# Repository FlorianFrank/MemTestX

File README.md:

<div style="text-align: center;">  </div>

</br>

This work is based on the publication **Reconfigurable Hardware Platform for Characterizing Physical Unclonable Functions in Non-Volatile Memories**, which is currently under review:

> **Abstract:**  
> Physical Unclonable Functions (PUFs) are widely recognized for deriving strong cryptographic keys from inherent manufacturing variations in hardware.  
> A popular class of PUFs is extracted from memory modules already integrated into computing systems, offering a cost-efficient method for generating strong cryptographic keys. Various techniques exist for extracting PUF responses from such memory modules, including repeated row activation and exploitation of charge leakage effects (known as row hammering), variations in supply voltage, intentional violations of memory timing specifications, as well as the use of random startup values and data retention characteristics. To perform such experiments—especially on novel non-volatile memory modules—a dedicated measurement ecosystem is required, which is presented in this work. The proposed setup uses a custom PCB to connect different types of memories to reconfigurable hardware. An optimized hardware design was developed and deployed on the reconfigurable hardware, enabling the execution of PUF experiments on various memory modules. The system allows for dynamic adjustment of timing specifications and voltage levels, even during experiment execution. Finally, a program is provided that schedules the experiments, retrieves the results, and enables persistent storage and evaluation methods.

This repository contains all components required for an extensive evaluation of memory-based PUFs, with a focus on emerging memory technologies such as FRAM, MRAM, and ReRAM. The setup is built based on an AMD ZCU102 FPGA and is designed to interface with any memory device featuring an SRAM-compatible parallel interface.

The various components included in this repository are illustrated in the following figure:

<div style="text-align: center;">  </div>

The components are divided into **hardware** and **software** components, following the structure of this repository.  

### Hardware

The **hardware** folder contains:  

- **FMC Adapter PCB Layout:**  
  A PCB adapter designed to interface various memory modules with the ZCU102 through its FMC connector. It supports memories with up to 24 address lines and 16 data lines and bridges the logic voltage level differences between the ZCU102 and the connected memory modules. Additionally, it provides options for connecting external power supplies and includes debugging interfaces. The design prioritizes signal integrity and minimizes glitches and noise.

- **Memory Adapter Reference Design:**
A reference adapter board currently configured for the Lapis Semiconductor MR48V256C memory module, designed to interface with the FMC adapter PCB. This folder contains a short tutorial on how to adjust the board for other memory footprints.

- **FPGA Design:**  
  Contains the FPGA design implementing a custom SRAM memory controller with all timing parameters adjustable at runtime. It supports several types of experiments, including rowhammering as well as read and write latency variations. Timing parameters can be tuned with a granularity of 2.5 nanoseconds. The design also includes an AXI interface for communication with the ZCU102’s processing system.

### Software

The **software** folder contains:  

- **PS Software:**  
  Implements the firmware running on the Processing System (PS) of the ZCU102. It manages communication with the PL to schedule and control experiments, as well as to receive measurement data through the same interface.  
  Additionally, it provides a network interface for receiving commands and parameters from an external experiment scheduler (described below). The firmware also transmits the collected measurement data back to this external program for persistent storage and further analysis.

- **Experiment Scheduler:**  
  A program that runs on an external computer connected to the ZCU102 via Ethernet. It allows the definition of various experiments and hardware classes (e.g., specific memory models), as well as instances of those classes. The scheduler manages the execution of experiments on these instances, delegating them either to the PS Software on the ZCU102 or to a microcontroller-based reference setup (described next).  
  It also collects the resulting measurement data, stores it persistently, and keeps track of the experiments executed for each hardware instance.

- **Microcontroller-Based Setup:**  
  An implementation running on an STM32F429 microcontroller with an integrated memory controller, capable of executing the same set of experiments as the ZCU102. However, this setup is constrained by the significantly lower clock frequency of its memory controller (120 MHz compared to 400 MHz on the FPGA). Communication with the experiment scheduler is established via a UART interface.

- **GUI support:**

## Quick Setup

The following provides the basic information to setup the memory evaluator. 

### Prerequisites

To build the PCB, **KiCad version 6** is required.  
To build the FPGA design and PS firmware, **Xilinx Vivado 2022.2** with **Vitis** must be installed as well as a **CMake** build system.
Note that generating the bitstream for the **ZCU102** requires the **Vivado ML Enterprise Edition**.  

The scheduler requires at least **Python 3.10**.  

A detailed list of all dependencies can be found in the respective component folders.

### PCB Production

To produce the PCB, navigate to `hardware/pcbs/fmc_memory_adapter`. The export folder contains the compressed Gerber files, which can be uploaded to your preferred PCB manufacturer.
The required components are listed in the **bill_of_material** folder.

### MPSoC Setup

To set up the FPGA and the corresponding firmware on the processing system, we provide a script that automates all required steps.  
Simply run the following commands:

```bash
cd scripts
./setup_and_run_environment.sh
```

This script performs the steps illustrated in the following diagram:

<div style="text-align: center;">  </div>

> ⚠️ This script has been verified only on **Ubuntu 22.10**, with **Vivado** installed in `/opt/Xilinx`.  
> To run it in a different environment, adjustments to the `VIVADO_PATH` variable or direct execution of the `.tcl` scripts may be necessary.

Furthermore, as shown in the figure above, the `./setup_and_run_environment.sh` script directly invokes several other scripts displayed at the bottom.  
These scripts can also be executed manually.  
Additional information about each script can be found in the respective folders containing them.

### Microcontroller-based Setup

To compile the microcontroller-based setup located in `software/memory_evaluator_stm32f429`, we provide a Docker-based build process.  
This approach eliminates the need to install the full toolchain on your local machine.  

First, build the Docker image by running:

```bash
cd software/memory_evaluator_stm32f429
docker build -t stm32f429-build .
```

Then, compile the firmware by executing:

```bash
./compile_fw_docker.sh
```

This command will start the Docker container, compile the firmware, and copy the resulting `MemoryController.elf` into the `software/memory_evaluator_stm32f429/bin` folder.

To flash the device, OpenOCD integrated within the CLion IDE was used. For more details, refer to the [`README.md`](/software/memory_evaluator_stm32f429/README.md) file found within the respective folder.

### Run the Scheduler (standalone)

All necessary dependencies for the scheduler can be installed by running:

```bash
cd software/experiment_scheduler/scripts
./setup.sh
```

To start the scheduler, simply execute:

```bash
cd software/experiment_scheduler/scripts
./run.sh <test_specification>.yaml
```

More information about the test specification format can be found in the scheduler’s [`README.md`](/software/experiment_scheduler/README.md) file.

### Run the Scheduler (with GUI Support)

Our microcontroller can be connected to a graphical user interface to define tests, schedule and monitor their execution.

#### Checkout the Backend and GUI 

If you are working from the Zenodo archive, you need to manually clone the backend and GUI:

```bash
cd software
git clone git@github.com:FlorianFrank/experiment_execution_hub.git
cd experiment_execution_hub
git sumbmodule update --init --recursive
```
If you instead cloned the GitHub repository with submodules, the backend and GUI are already present in the software folder and no additional setup is required.

#### Start the Backend and GUI

From inside the ```experiment_execution_hub``` directory, start the Django backend and the React frontend using Docker:

```bash
docker compose up
```
This will launch the: 
  - nats broker to connect multiple schedulers with the GUI
  - the Django backend (API and services), and
  - the React frontend (web-based GUI).

Afterwards you can see the gui when opening

[http://localhost:8000](http://localhost:8000)

Detailed information can be found in the repositories documentation [https://github.com/FlorianFrank/experiment_execution_hub](https://github.com/FlorianFrank/experiment_execution_hub)

as well as on a decicated documentation website [https://test-automation.florian-frank.com](https://test-automation.florian-frank.com)

To run the microservice go to ```software/experiment_scheduler``` from the root direcory and simply run:

```bash
./run_microservice.bash
```

Make sure the microservice is configured the right way (see the dedicated documentation in ```software/experiment_scheduler```)

## Contact

If you encounter any issues or errors, please open an issue on this page or contact me at:  **florian.frank(at)uni-passau.de**

## Release Notes
---

See the [changelog](CHANGELOG.md) for changes between versions.

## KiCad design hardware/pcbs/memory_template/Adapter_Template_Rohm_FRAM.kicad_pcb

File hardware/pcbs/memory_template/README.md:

### Memory Template PCB Design

This directory contains a reference adapter board design that can be adapted to different memory types. The current implementation targets the [Lapis Semiconductor MR48V256C](https://www.mouser.de/datasheet/2/348/ROHM-06-04-2018-FEDR48V256C-01-1500402.pdf) FRAM memory module.

A 3D rendering of the board is shown below:

#### Customization for Other Memory Modules
To adapt the design to a different memory device (including alternative packages):

1. Open the KiCad Project (`Adapter_Template_Rohm_FRAM.pro`)

The design was created using **KiCad 8.0.7.**

2. Open the schematic 
    - Identify the two 2×32-pin connectors on the left and right:
        - These connect to the FMC adapter board.
        - **Do not modify these connectors.**
    - Locate the symbol reprenting the memory module in the center: 
        - Either modify the symbol to fit your footprint or
        - adjust the footprint to match the existing symbol

The schematic is shown below for reference:

3. Open the Footprint Editor in KiCad.

To adapt the footprint: 

- Create a new footprint or import an existing one (e.g. from [Component Search Engine](https://componentsearchengine.com))
- Now adjust the pad number so that they match with the ones from the symbol as shown below.

4. Assign the footprint to Symbol U2

5. Export the Netlist `File -> Export -> Netlist``

6. Open the PCB design (`Adapter_Template_Rohm_FRAM.kicad_pcb`)

7. Import the netlist and route the design. 
    > Rooting may be automized for example by using [freerouting](https://www.freerouting.app)

Figure of the reference PCB design: 

8. Now you can export your Design as Gerber file and produce it as cost efficient two layer PCB.

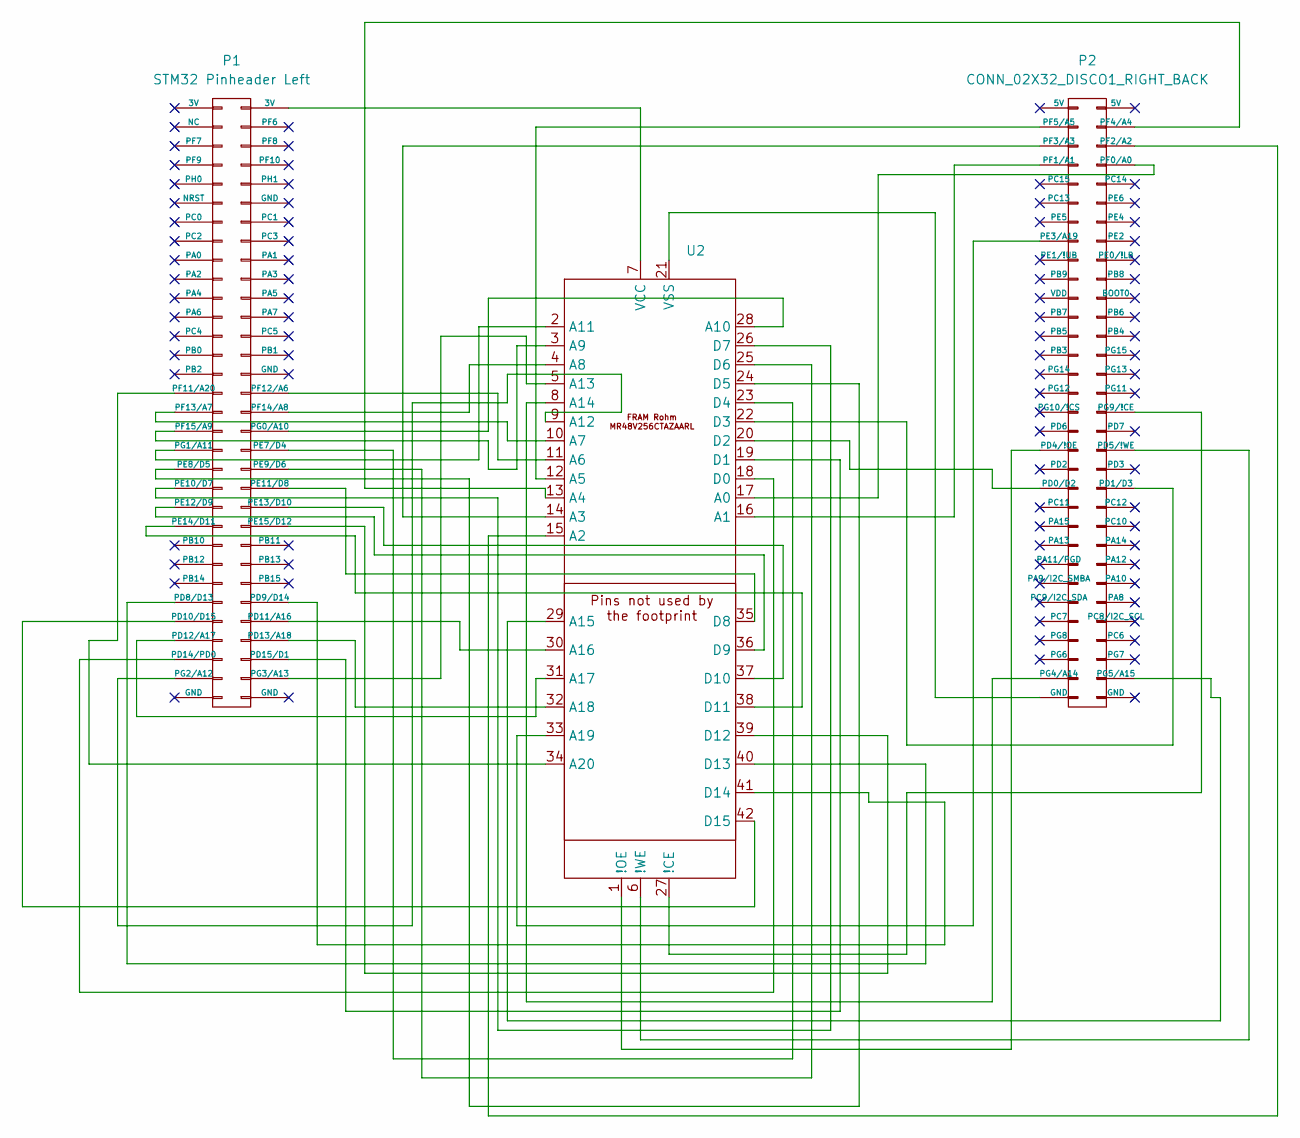
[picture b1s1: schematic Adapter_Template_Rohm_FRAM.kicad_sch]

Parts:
P1: STM32 Pinheader Left; PinHeader_2x32_P2.54mm_Vertical
P2: CONN_02X32_DISCO1_RIGHT_BACK; PinHeader_2x32_P2.54mm_Vertical
U2: TSOP-1 MR48V256CTAZAARL

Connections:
unnamed: P1.53 (PD8/D13), U2.40 (D13)
unnamed: P1.54 (PD9/D14), U2.41 (D14)
unnamed: P1.55 (PD10/D15), U2.42 (D15)
unnamed: P1.56 (PD11/A16), U2.30 (A16)
unnamed: P1.57 (PD12/A17), U2.31 (A17)
unnamed: P1.58 (PD13/A18), U2.32 (A18)
unnamed: P1.59 (PD14/PD0), U2.18 (D0)
unnamed: P1.60 (PD15/D1), U2.19 (D1)
unnamed: P1.38 (PE7/D4), U2.23 (D4)
unnamed: P1.39 (PE8/D5), U2.24 (D5)
unnamed: P1.40 (PE9/D6), U2.25 (D6)
unnamed: P1.41 (PE10/D7), U2.26 (D7)
unnamed: P1.42 (PE11/D8), U2.35 (D8)
unnamed: P1.43 (PE12/D9), U2.36 (D9)
unnamed: P1.44 (PE13/D10), U2.37 (D10)
unnamed: P1.45 (PE14/D11), U2.38 (D11)
unnamed: P1.46 (PE15/D12), U2.39 (D12)
unnamed: P1.31 (PF11/A20), U2.34 (A20)
unnamed: P1.32 (PF12/A6), U2.11 (A6)
unnamed: P1.33 (PF13/A7), U2.10 (A7)
unnamed: P1.34 (PF14/A8), U2.4 (A8)
unnamed: P1.35 (PF15/A9), U2.3 (A9)
unnamed: P1.36 (PG0/A10), U2.28 (A10)
unnamed: P1.37 (PG1/A11), U2.2 (A11)
unnamed: P1.61 (PG2/A12), U2.9 (A12)
unnamed: P1.62 (PG3/A13), U2.5 (A13)
unnamed: P2.41 (PD0/D2), U2.20 (D2)
unnamed: P2.42 (PD1/D3), U2.22 (D3)
unnamed: P2.37 (PD4/!OE), U2.1 (!OE)
unnamed: P2.38 (PD5/!WE), U2.6 (!WE)
unnamed: P2.15 (PE3/A19), U2.33 (A19)
unnamed: P2.8 (PF0/A0), U2.17 (A0)
unnamed: P2.7 (PF1/A1), U2.16 (A1)
unnamed: P2.6 (PF2/A2), U2.15 (A2)
unnamed: P2.5 (PF3/A3), U2.14 (A3)
unnamed: P2.4 (PF4/A4), U2.13 (A4)
unnamed: P2.3 (PF5/A5), U2.12 (A5)
unnamed: P2.61 (PG4/A14), U2.8 (A14)
unnamed: P2.62 (PG5/A15), U2.29 (A15)
unnamed: P2.34 (PG9/!CE), U2.27 (!CE)
unnamed: P1.2 (3V), U2.7 (VCC)
unnamed: P2.63 (GND), U2.21 (VSS)

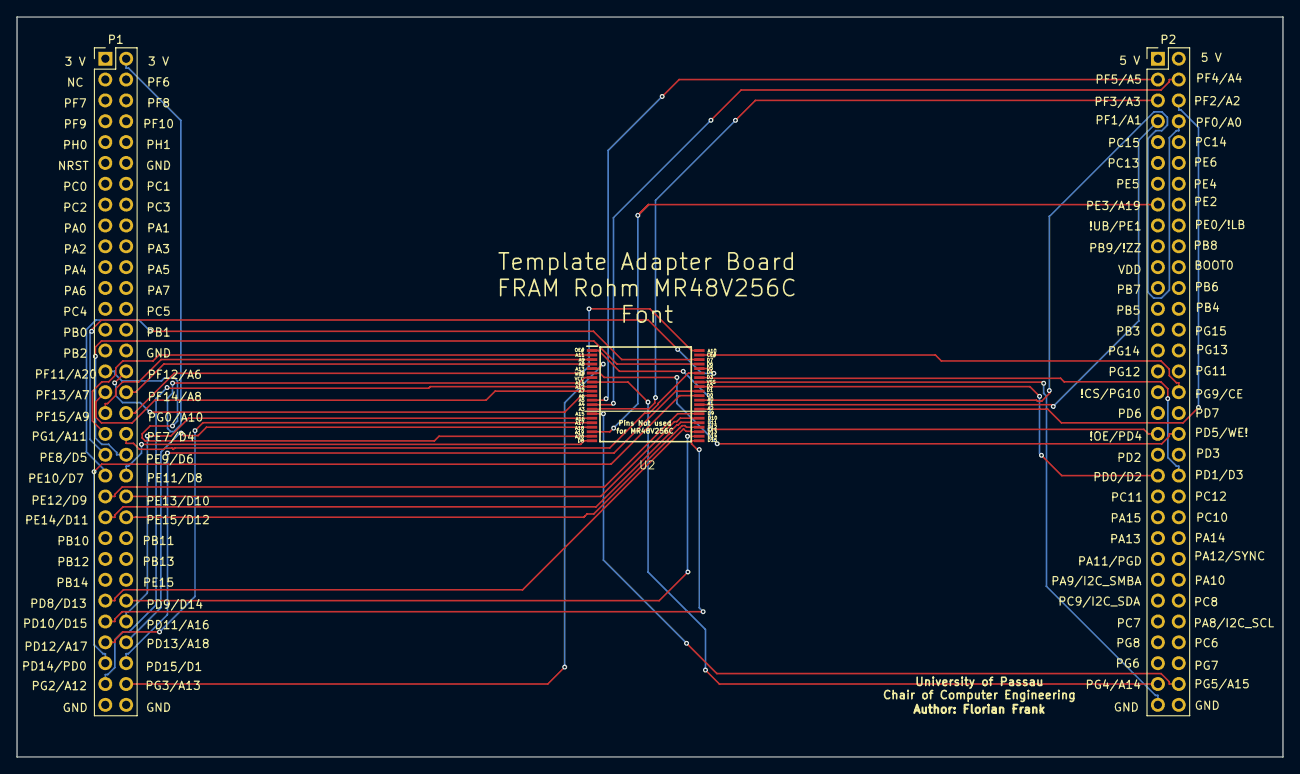
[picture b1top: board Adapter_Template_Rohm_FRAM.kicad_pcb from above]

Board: 2 copper layers, 154.3 x 90.2 mm, 3 parts (0 on the bottom side), 42 nets.

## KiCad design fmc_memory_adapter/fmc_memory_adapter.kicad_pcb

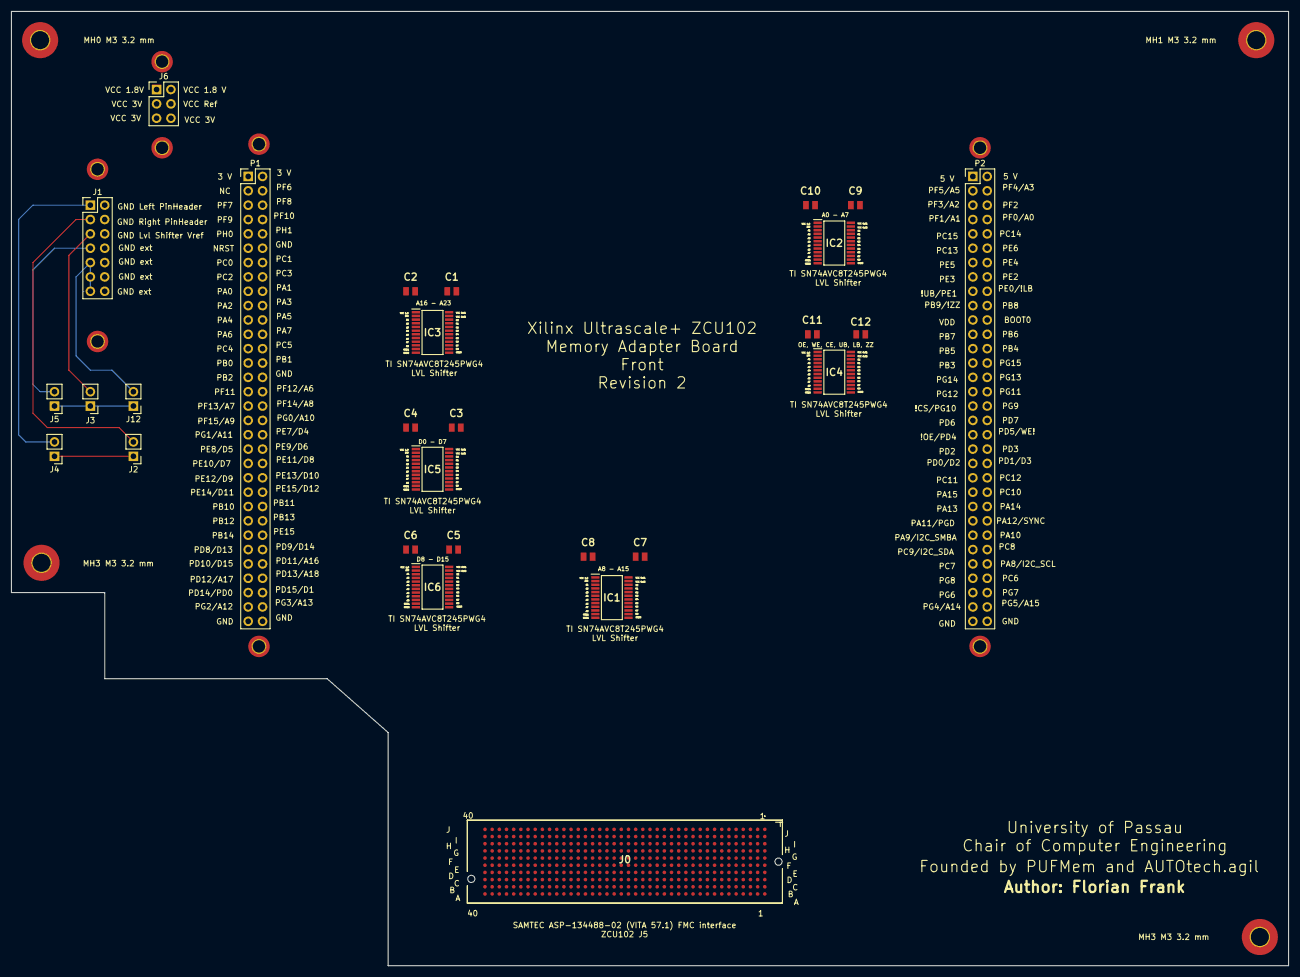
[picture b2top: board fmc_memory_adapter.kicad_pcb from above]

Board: 2 copper layers, 226.1 x 168.9 mm, 40 parts (0 on the bottom side), 109 nets.

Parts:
 : MountingHole_2.2mm_M2_DIN965_Pad_TopBottom
 #2,  #3,  #4,  #5,  #6,  #7,  #8: MountingHole_2.2mm_M2_DIN965_Pad_TopBottom
C1, C2, C3, C4, C5, C6, C7, C8, C9, C10, C11, C12: C0805C104K5RAC7411; CAPC2012X88N
IC1, IC2, IC3, IC4, IC5, IC6: SN74AVC8T245PWG4; SOP65P640X120-24N
J0: ASP-134488-02; ASP13448802
J1: Conn_02x07_Odd_Even; PinHeader_2x07_P2.54mm_Vertical
J2: GND_Jumper2; PinHeader_1x02_P2.54mm_Vertical
J3: GND_Jumper3; PinHeader_1x02_P2.54mm_Vertical
J4: GND_Jumper1; PinHeader_1x02_P2.54mm_Vertical
J5: GND_Jumper4; PinHeader_1x02_P2.54mm_Vertical
J6: Voltage_Selector; PinHeader_2x03_P2.54mm_Vertical
J12: GND_Jumper5; PinHeader_1x02_P2.54mm_Vertical
MH0 M3 3.2 mm, MH1 M3 3.2 mm, MH3 M3 3.2 mm, MH3 M3 3.2 mm#2: MountingHole_3.2mm_M3_Pad_TopBottom
P1: CONN_02X32_DISCO1_LEFT_BACK; PinHeader_2x32_P2.54mm_Vertical
P2: CONN_02X32_DISCO1_RIGHT_BACK; PinHeader_2x32_P2.54mm_Vertical

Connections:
unnamed: IC1.3 (A1), J0.G6
unnamed: IC1.4 (A2), J0.G7
unnamed: IC1.5 (A3), J0.G9
unnamed: IC1.6 (A4), J0.G10
unnamed: IC1.7 (A5), J0.G12
unnamed: IC1.8 (A6), J0.G13
unnamed: IC1.9 (A7), J0.G15
unnamed: IC1.10 (A8), J0.G16
unnamed: IC1.21 (B1), P1.34 (PF14)
unnamed: IC1.20 (B2), P1.35 (PF15)
unnamed: IC1.19 (B3), P1.36 (PG0)
unnamed: IC1.18 (B4), P1.37 (PG1)
unnamed: IC1.17 (B5), P1.61 (PG2)
unnamed: IC1.16 (B6), P1.62 (PG3)
unnamed: IC1.15 (B7), P2.61 (PG4)
unnamed: IC1.14 (B8), P2.62 (PG5)
unnamed: IC1.2 (DIR), IC2.2 (DIR), IC3.2 (DIR), IC4.2 (DIR), J0.H10
unnamed: C1.2, C2.2, C3.1, C4.1, C5.1, C6.1, C7.1, C8.1, C9.1, C10.1, C11.1, C12.1, IC1.11 (GND_1), IC1.12 (GND_2), IC1.13 (GND_3), IC2.11 (GND_1), IC2.12 (GND_2), IC2.13 (GND_3), IC3.11 (GND_1), IC3.12 (GND_2), IC3.13 (GND_3), IC4.11 (GND_1), IC4.12 (GND_2), IC4.13 (GND_3), IC5.11 (GND_1), IC5.12 (GND_2), IC5.13 (GND_3), IC6.5 (A3), IC6.11 (GND_1), IC6.12 (GND_2), J0.D8, J1.6
unnamed: C2.1, C3.2, C4.2, C5.2, C8.2, C9.2, C12.2, IC1.1 (VCCA), IC2.1 (VCCA), IC3.1 (VCCA), IC4.1 (VCCA), IC5.1 (VCCA), IC6.1 (VCCA), IC6.23 (VCCB_1), IC6.24 (VCCB_2), J6.2
unnamed: C1.1, C6.2, C7.2, C10.2, C11.2, IC1.23 (VCCB_1), IC1.24 (VCCB_2), IC2.23 (VCCB_1), IC2.24 (VCCB_2), IC3.23 (VCCB_1), IC3.24 (VCCB_2), IC4.23 (VCCB_1), IC4.24 (VCCB_2), IC5.23 (VCCB_1), IC5.24 (VCCB_2), J6.4
unnamed: IC1.22 (~OE), IC2.22 (~OE), IC3.22 (~OE), IC4.22 (~OE), IC5.22 (~OE), IC6.22 (~OE), J0.H7
unnamed: IC2.3 (A1), J0.D17
unnamed: IC2.4 (A2), J0.D18
unnamed: IC2.5 (A3), J0.D20
unnamed: IC2.6 (A4), J0.D21
unnamed: IC2.7 (A5), J0.D23
unnamed: IC2.8 (A6), J0.D24
unnamed: IC2.9 (A7), J0.D26
unnamed: IC2.10 (A8), J0.D27
unnamed: IC2.21 (B1), P2.8 (PF0)
unnamed: IC2.20 (B2), P2.7 (PF1)
unnamed: IC2.19 (B3), P2.6 (PF2)
unnamed: IC2.18 (B4), P2.5 (PF3)
unnamed: IC2.17 (B5), J1.4, P2.4 (PF4), P2.63 (GND), P2.64 (GND)
unnamed: IC2.16 (B6), P2.3 (PF5)
unnamed: IC2.15 (B7), P1.32 (PF12)
unnamed: IC2.14 (B8), P1.33 (PF13)
unnamed: IC3.3 (A1), J0.G18
unnamed: IC3.4 (A2), J0.G19
unnamed: IC3.5 (A3), J0.G21
unnamed: IC3.6 (A4), J0.G22
unnamed: IC3.7 (A5), J0.G24
unnamed: IC3.8 (A6), J0.G25
unnamed: IC3.9 (A7), J0.G27
unnamed: IC3.10 (A8), J0.G28
unnamed: IC3.21 (B1), P1.56 (PD11)
unnamed: IC3.20 (B2), P1.57 (PD12)
unnamed: IC3.19 (B3), P1.58 (PD13)
unnamed: IC3.18 (B4), P2.15 (PE3)
unnamed: IC3.17 (B5), P1.31 (PF11)
unnamed: IC3.16 (B6), P2.30 (PG13)
unnamed: IC3.15 (B7), P2.28 (PG15)
unnamed: IC3.14 (B8), P2.26 (PB4)
unnamed: IC4.3 (A1), J0.G30
unnamed: IC4.4 (A2), J0.G31
unnamed: IC4.5 (A3), J0.G33
unnamed: IC4.6 (A4), J0.G34
unnamed: IC4.7 (A5), J0.G36
unnamed: IC4.8 (A6), J0.G37
unnamed: IC4.21 (B1), P2.37 (PD4)
unnamed: IC4.20 (B2), P2.38 (PD5)
unnamed: IC4.19 (B3), P2.34 (PG9)
unnamed: IC4.18 (B4), P2.18 (PE0)
unnamed: IC4.17 (B5), P2.17 (PE1)
unnamed: IC4.16 (B6), P2.19 (PB9)
unnamed: IC5.3 (A1), J0.C10
unnamed: IC5.4 (A2), J0.C11
unnamed: IC5.5 (A3), J0.C14
unnamed: IC5.6 (A4), J0.C15
unnamed: IC5.7 (A5), J0.C18
unnamed: IC5.8 (A6), J0.C19
unnamed: IC5.9 (A7), J0.C22
unnamed: IC5.10 (A8), J0.C23
unnamed: IC5.21 (B1), P1.59 (PD14)
unnamed: IC5.20 (B2), P1.60 (PD15)
unnamed: IC5.19 (B3), P2.41 (PD0)
unnamed: IC5.18 (B4), P2.42 (PD1)
unnamed: IC5.17 (B5), P1.38 (PE7)
unnamed: IC5.16 (B6), P1.39 (PE8)
unnamed: IC5.15 (B7), P1.40 (PE9)
unnamed: IC5.14 (B8), P1.41 (PE10)
unnamed: IC5.2 (DIR), IC6.2 (DIR), J0.H8
unnamed: IC6.3 (A1), J0.C26
unnamed: IC6.4 (A2), J0.C27
unnamed: IC6.6 (A4), J0.D9
unnamed: IC6.7 (A5), J0.D11
unnamed: IC6.8 (A6), J0.D12
unnamed: IC6.9 (A7), J0.D14
unnamed: IC6.10 (A8), J0.D15
unnamed: IC6.21 (B1), P1.42 (PE11)
unnamed: IC6.13 (GND_3), IC6.20 (B2), P1.43 (PE12)
unnamed: IC6.19 (B3), P1.44 (PE13)
unnamed: IC6.18 (B4), P1.45 (PE14)
unnamed: IC6.17 (B5), P1.46 (PE15)
unnamed: IC6.16 (B6), P1.53 (PD8)
unnamed: IC6.15 (B7), P1.54 (PD9)
unnamed: IC6.14 (B8), P1.55 (PD10)
unnamed: J1.1, J4.2
unnamed: J1.2, P1.30 (GND), P1.63 (GND), P1.64 (GND)
unnamed: J1.3, J2.2
unnamed: J1.5, J3.2
unnamed: J1.7, J5.2
unnamed: J1.9, J1.11, J1.13, J12.2
unnamed: J0.C34, J2.1, J4.1
unnamed: J0.H11, J6.1
unnamed: J0.D36, J6.3
unnamed: J0.C39, J6.5
unnamed: J6.6, P1.1 (3V), P1.2 (3V)
unnamed: J0.D35, J3.1, J5.1, J12.1

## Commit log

2025-06-08 Add schematic for FMC memory Adapter
2025-06-08 Add do not place markers to schematics
2025-06-10 Update schematics and footprints
2025-06-10 Update PCB File
2025-06-10 Update Schematic
2025-06-10 Add README.md to the repository
2025-06-10 Add mechanical support to the repo
2025-06-10 Add memory test controller to repo
2025-06-10 Add license
2025-06-10 Move license to top directory
2025-10-11 Add schematics and fmc controller
2025-10-14 Add .gitignore for KiCad projects
2025-10-14 Add footprints and change folders for KiCad PCB
2025-10-14 Add 3D printed mechanical support
2025-10-14 Add docs folder and README.md
2025-10-14 Add Description of Pin connections from J5
2025-10-14 Add bom to README.md
2025-10-14 Add Total Price to BOM list
2025-10-14 Add total price
2025-10-14 Add missing parts and ground and voltage connectors
2025-10-14 Add description of transceiver pinout
2025-10-14 Add Dual Transceiver Pins
2025-10-14 Add short description of the transceivers
2025-10-14 change color of transceiver connection
2025-10-14 Make fmc memory module fill the whole page
2025-10-15 Add PCI-E debugging interface connector to PCB
2025-10-15 improve debuging port readme
2025-10-15 Add figures showing how to connect the jumpers
2025-10-16 Add descrption on how to mount the mechanical support
2025-10-16 Add testing and revision history section
2025-10-16 Update bill of materials
2025-10-16 Add bill of materials
2025-10-16 Add screws and spacers to bom
2025-10-16 Udpate total price
2025-10-16 Update PCB
2025-10-16 Add source files, build scripts, simulation files and block design files
2025-10-16 Define constraints file
2025-10-16 Add constraints file to create_project.tcl. Add shell script allowing to create the project
2025-10-16 Add AXI IP Core
2025-10-16 Remove unnecessary PCB folder
2025-10-16 Update create_project script
2025-10-16 Add docuementation of FPGA implementation
2025-10-16 Add description on how to setup the project and chagne background color of block design
2025-10-16 Add figure showing the full simulation
2025-10-17 Fix some typos and add documentation
2025-10-17 Add journal and log to gitignore
2025-10-17 Fix eror in creation script
2025-10-17 Rename puf execution controller
2025-10-17 Add file description blocks
2025-10-17 Fix some minor bugs
2025-10-17 Add highlighting for erorrs and warnings
2025-10-17 Fix color coding
2025-10-17 Add missing }
2025-10-17 Add colon for pattern matching
2025-10-17 Fix errors in main block design
2025-10-17 Change numer of clock outputs to 2
2025-10-17 Uncomment ignored parameters in block design
2025-10-17 Generate HDL Wrapper from block design when running create project
2025-10-17 Update make_hdl wrapper commend
2025-10-17 Add script to generate bitstream
2025-10-17 Fix incorrect check in create_bitstream.sh
2025-10-17 Fix block design loading
2025-10-17 Enable constraints file in project
2025-10-17 Update optimization and implementation
2025-10-17 Remove unnecessary checks
2025-10-17 Use existing runs for impl and synth
2025-10-17 First open synth before writing checkpoint
2025-10-17 Rename create_bitstream to generate_bitstream
2025-10-17 Remove unnecessary test scheduler folder
2025-10-17 Add stm32f429 reference implementation
2025-10-18 Improve grounding in pcb design
2025-10-18 Update footprints
2025-10-20 Fix error in hdl wrapper selection
2025-10-20 Update BOM
2025-10-20 Fix errors in generate_bitstream script and adjust README.md
2025-10-20 Add PS Firmware to the repository
2025-10-20 Add toolchain file and CMakeLists.txt
2025-10-20 Add build bash script
2025-10-20 Add command to export hardware platform
2025-10-20 Add README.md describing the content of the software folder
2025-10-20 Add main README.md
2025-10-20 Add description of software components to README.md
2025-10-20 Update overview image
2025-10-20 Add description on how to start the scheduler
2025-10-20 Remove unnecessary >s
2025-10-23 Add script to build and export platform
2025-10-23 Adjust paths in cmake and AXI define from xparameters
2025-10-23 Fix undefined sleep reference
2025-10-23 Add script to flash the ZCU102
2025-10-23 Add script to flash the build elf file on the Cortex A53
2025-10-23 Fix logging and add install directory
2025-10-23 Add build script to repository
2025-10-23 Add script to build and compile the hardware design and flash the CPU
2025-10-23 Add test scheduler to the repository
2025-10-23 Rename test_scheduler to experiment_scheduler
2025-10-23 Add figure showing the build pipeline
2025-10-24 Export test configuration to yaml file
2025-10-24 Add requirements
2025-10-24 Add necessary files from test framework
2025-10-24 Add README describing the the configuration and test execution
2025-10-24 Add pyinstrument control lib as submodule
2025-10-24 Add command line parameter to run script
2025-10-24 Add new voltage variation test script and a refresh memory command line parameter
2025-10-24 Minor improvements
2025-10-24 Update stm32 firmware to most recent version
2025-10-24 Add build description of STM32F429 to README.md
2025-10-25 Fix error of incorrect quote char
2025-10-30 Update pcb design
2025-10-30 Update figures
2025-11-12 Update README for ps firmware
2025-11-12 Add README and figures to ps_software
2025-11-12 Add picture of adapter pcb board
2025-11-12 Add Figure of test scheduler
2025-11-12 Center figures
2025-11-12 Remove unnecessary DIV
2025-11-12 Update README.md in experiment scheduler
2025-11-12 Add changelog to repository
2025-11-12 Add figures and update README.md
2025-11-12 Improve central README.md
2025-11-12 Add gerber files
2025-11-12 Recenter figures in README.md
2025-11-12 Add Graphical abstract
2025-11-12 Add abstract and paper title
2025-11-24 Add missing component.xml
2025-11-24 Fix bug. Create platform folder if not available
2025-11-24 Include simulation files when creating project
2025-11-24 fix bug in block design
2025-11-25 Add script to automatically run simulation
2025-11-25 Update simulation script
2025-11-25 add setup and build scripts
2025-11-25 Add file explaining how to extract a simulation configuration
2025-11-25 Update Generation of Simulation Samples section
2025-11-25 Update command handler IP core
2025-11-25 Fix timestamp and set server IP
2025-11-25 Improve formatting and some minor issues in ps firmware
2025-11-25 Add evaluation files
2025-11-25 Update evaluation scripts
2025-11-26 Add Jupyter notebook for evaluation and update evaluation scripts
2025-11-26 Add pickle test files
2025-11-26 Include measurement data of voltage variations
2025-11-26 Add memory controller timing values
2025-11-27 Add ZCU102 meausurements
2025-11-27 Add db merger tool
2025-11-27 Refactor evaluation
2025-11-27 Fix remaining errors in README.md within the pcb folder
2025-11-27 Update csv file with fonts exported as shapes
2025-11-27 Update repository logo
2025-11-27 Move logo a bit up
2025-11-28 Update repository logo as vector graphics
2025-11-28 Update software README.md's
2025-11-28 Fix cut of pcb adapter figure
2025-11-29 Increase databus size and address bus size
2025-11-29 Remove non necessary register in IO_MUX
2025-11-29 Update test benches and remove unnecessary ones
2025-11-29 Update block designes
2025-11-29 Add legacy CMake to allow compilation on Vitis 2022.1
2025-11-29 Add sample row hammerin test to tb_axi_full.sv
2025-11-29 Fix error of incorrect range of init_value
2025-12-01 Add additional documentation
2025-12-01 Remove unused file tests.py
2025-12-01 Update README.md of PS Software
2025-12-01 Add Changelog
2025-12-05 Put the hardware design under CERN Open Hardware Licence Version 2
2025-12-05 Fix pcb design
2025-12-05 Remove unnecessary backup files and swap files
2026-02-11 Add microservice to test scheduler
2026-02-11 Fix execution of iterations, progress based by comparing the currently processed address with the received address range and do further improvements.
2026-02-11 Add simulator to test the interaction with the scheduler.
2026-02-11 Update README.md with new information regarding the mircoservice and simulator
2026-02-11 Add simple microservice config
2026-02-11 Add figure showing a detected container in the GUI
2026-02-12 Minor refactoring and cleanup. Fix missing hammering iterations variable.
2026-02-12 Add puf hub backend and frontend to the repository
2026-02-13 Update Documentation
2026-03-17 Add template memory adapter
2026-03-18 Add README.md and remaining pcb files
2026-03-18 Update root README.md, adding new information about the reference memory adapter
2026-03-21 Add ER diagram and descripiton to scheduler ER diagram
2026-03-21 Add white background to ER diagram
2026-03-21 Reduce margin of ER diagram
